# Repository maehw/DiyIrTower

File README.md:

# README

Can be used as a replacement of the original LEGO IR serial tower with programs and platforms such as

* [WebPBrick](https://www.webpbrick.com): web-based NQC IDE (see also: [github.com/maehw/WebPBrick/](https://github.com/maehw/WebPBrick/))
* [Bricx Command Center (BricxCC)](https://bricxcc.sourceforge.net/): 32-bit Windows IDE
* `firmdl3` command line download tool
* probably other software

to **load user programs and firmware** on the yellow LEGO Mindstorms RCX programmable brick.

## Hardware

> ⚠️ **Warning**: Exposure to infrared light can cause harm to humans. Prolonged or intense exposure may lead to damage to the eyes or skin. Always use proper safety equipment when working with infrared light sources. Make sure to limit the current through the infrared TX LED!

### Pin Assignment

At the heart of the DIY solution, there's an 8-pin ATtiny13A microcontroller.

Pin Assignment Table for the ATtiny13A:

| IC Pin | Pin    | Purpose              | Direction | Side of IC | ISP Usage |
|--------|--------|----------------------|-----------|------------|-----------|
| 1      | PB5    | Reset                | Unused    | Left       | Reset     |
| 2      | PB3    | IR_LED_TX_PIN        | Output    | Left       |           |
| 3      | PB4    | PHOTO_RX_PIN         | Input     | Left       |           |
| 4      | GND    | Ground               | -         | Left       | GND       |
| 5      | PB0    | UART_RX_PIN          | Output    | Right      | MOSI      |
| 6      | PB1    | UART_TX_PIN          | Input     | Right      | MISO      |
| 7      | PB2    | IR_ACTIVITY_LED_PIN  | Output    | Right      | SCK       |
| 8      | VCC    | Supply Voltage (VCC) | -         | Right      | VCC       |

The column "ISP Usage" shows what pins need to be connected for programming ("flashing") by a 6-pin AVR _In-System Programmer_ (ISP).

### Hardware Parts

- ATtiny13A microcontroller as the "brain" (calibrated internal 9.6 MHz oscillator as clock source; other uCs such as the ATtiny85 _may_ work as they have more SRAM and more flash memory, but timing values will need to be adjusted)
- Vishay Semiconductors TSOP4338 or TSOP4838 38 kHz infrared receiver (others 38 kHz infrared receivers _may_ work)
- Vishay Semiconductors TSAL6200 940 nm infrared TX LED (others 940 nm infrared TX LEDs _may_ work)

If you've built a working DiyIrTower yourself with these or different parts, please let me know! The first design has used the TSOP4338. As it's not available everywhere, it has also been tested to work with the TSOP4838.

In my case, the circuitry is powered by a USB/serial converter cable which is also used to transfer the data over a virtual COM port (USB CDC interface). Please note that the converter cable of choice uses TTL voltage levels and not RS-232!

### Classic Breadboard

For the breadboard version see the image at the top. The Fritzing breadboard diagram looks as follows (please also pay attention to the hints inside the image):

### Solder Breadboard

An alternative would be a solder breadboard to make something semi-permanent (the green activity LED is hidden in the next photo between the jumper wires of the USB/serial converter cable):

### CAD PCB with KiCAD

Since January 2026, there's a KiCAD project with all necessary files (i.e. schematic, PCB layout, pre-generated Gerber files). So instead of putting the components together on a breadboard, a PCB can be ordered. At the time of writing, some prototype PCBs (Rev. 1.0) have been ordered. But I cannot guarantee, that the design is free of bugs.

I've decided to keep through-hole components, as they are easier to solder for beginners. It may make sense to add a DIP8 IC socket for the uC. The power and activity LEDs (and their resistors) are optional, as is the ISP header for initially flashing the IC. So a setup with the minimum of components would look like this:

By the way, I'd choose a rectangular connector for J1. Also, you'll have to bend the TX photo diode D2 sideways, so that it points to the same side as the IR receiver IC.

## Firmware

Find the productive firmware in folder `./firmware`.

### Prerequisites

- GNU C cross-compiler for AVR 8-bit `gcc-avr` (other build toolchains *may* work as well)
- `avrdude`: program for downloading and uploading the on-chip memories of AVR microcontrollers (or another similar tool)

### Build

To build, run:

```shell
avr-gcc -g -Wall -Os -mmcu=attiny13a -o main.elf main.c
```

_(Append the verbosity flag `-v` to see what's going on behind the scenes.)_

Want to check if it will it fit into the internal flash?

```shell
avr-size main.elf
   text	   data	    bss	    dec	    hex	filename
    776	      0	      7	    783	    30f	main.elf
```

Make sure to burn the microcontrollers fuses so that

- the calibrated internal 9.6 MHz oscillator is selected
- clock pre-scaler set to 1 (device is shipped with CKDIV8 programmed).

Reading fuses with avrdude (and in this case an `ehajo-isp` in-system programmer):

```shell
avrdude -c ehajo-isp -p t13a -U hfuse:r:-:h -U lfuse:r:-:h
```

The default values for the two fuse bytes of the ATtiny13A are `0xff` (high), `0x6a` (low).  The required settings however are: `0xff` (high), `0x7a` (low). Writing fuses with avrdude:

```shell
avrdude -c ehajo-isp -p t13a -U hfuse:w:0xff:m -U lfuse:w:0x7a:m
```

_(Hint: If the `avrdude` version being used gives *"avrdude: AVR Part "t13a" not found."*, try using `t13` instead of `t13a`.)_

Finally, flash the firmware:

```shell
avrdude -c ehajo-isp -p t13a -U flash:w:main.elf:e
```

### Test firmware

Please note that under `./test/firmware`, there are some more code files to test the assembled hardware. The commands from above can be reused, only the filename needs to be changed.

`blink.c` will blink the activity indication LED and hence allow to check if the LED is working and the compilation and flashing mechanisms also work.

`pulsed_ir_tx.c` will blink the activity indication LED and also transmit modulated infrared light at 38 kHz for 0.5 seconds and then switch the transmitter off for another 0.5 seconds. This allows to check if the fuse bytes have been set correctly or the blinking is way slower and the default `CKDIV8` may not have been overwritten.

`serial_echo.c` will _echo_ the serially received UART characters. Please note that this example does not make use of any uC UART peripheral but only relies upon GPIO pin edge detection on the "UART" receive pin. This can be used with any terminal emulator that works with serial devices or with the Python script `/test/scripts/serial_coms.py` to send and receive binary data:

```shell
$ python serial_coms.py -h
usage: serial_coms.py [-h] serial_device data_to_send

Send binary data over serial and receive response.

positional arguments:
  serial_device  Name of the serial device (e.g., '/dev/ttyUSB0')
  data_to_send   Binary data to send in HEX format (e.g., '55FF00609F609F')

options:
  -h, --help     show this help message and exit
```

Example:

```shell
$ python serial_coms.py /dev/ttyUSB0 11223344
[TX] 11 22 33 44 
[RX] 11 22 33 44
```

The same four bytes should be received that also have been transmitted before - just as you'd expect from an echo application! Check the command line output!

## Design details

The following timing diagram shows four signals from top to bottom:

* `UART_TX_PIN`: the UART transmit (=TX) signal - as sent by the PC, coming from the attached USB/serial converter
* `IR_LED_TX_PIN`: the modulated infrared transmit signal on the IR TX LED, on–off keying (OOK) modulated at 38 kHz, 38 kHz carrier is _active_ during _low_ periods of `UART_TX_PIN`
* `PHOTO_RX_PIN`: the signal on the (already demodulated) infrared receiver
* `UART_RX_PIN`: the UART receive (=RX) signal - as sent by the DIY IR tower to the USB/serial converter

The diagram shows the message `0x55 0xFF 0x00 0x10 0xEF 0x10 0xEF` being sent from the PC to the RCX (left half). It also shows the response from the RCX to the PC: `0x55 0xFF 0x00 0xEF 0x10 0xEF 0x10` (right half).

In the left half one can also see that the signal transmitted by the DIY IR tower is reflected and directly received by itself. This is due to the arrangement of IR TX LED and IR receiver - and afair can also be seen with the original IR towers. This "echo effect" must/can be handled in software!

Zooming in (less time for the same screen width) reveals the delays between the signals:

## Disclaimer

LEGO® is a trademark of the LEGO Group of companies which does not sponsor, authorize or endorse this project.

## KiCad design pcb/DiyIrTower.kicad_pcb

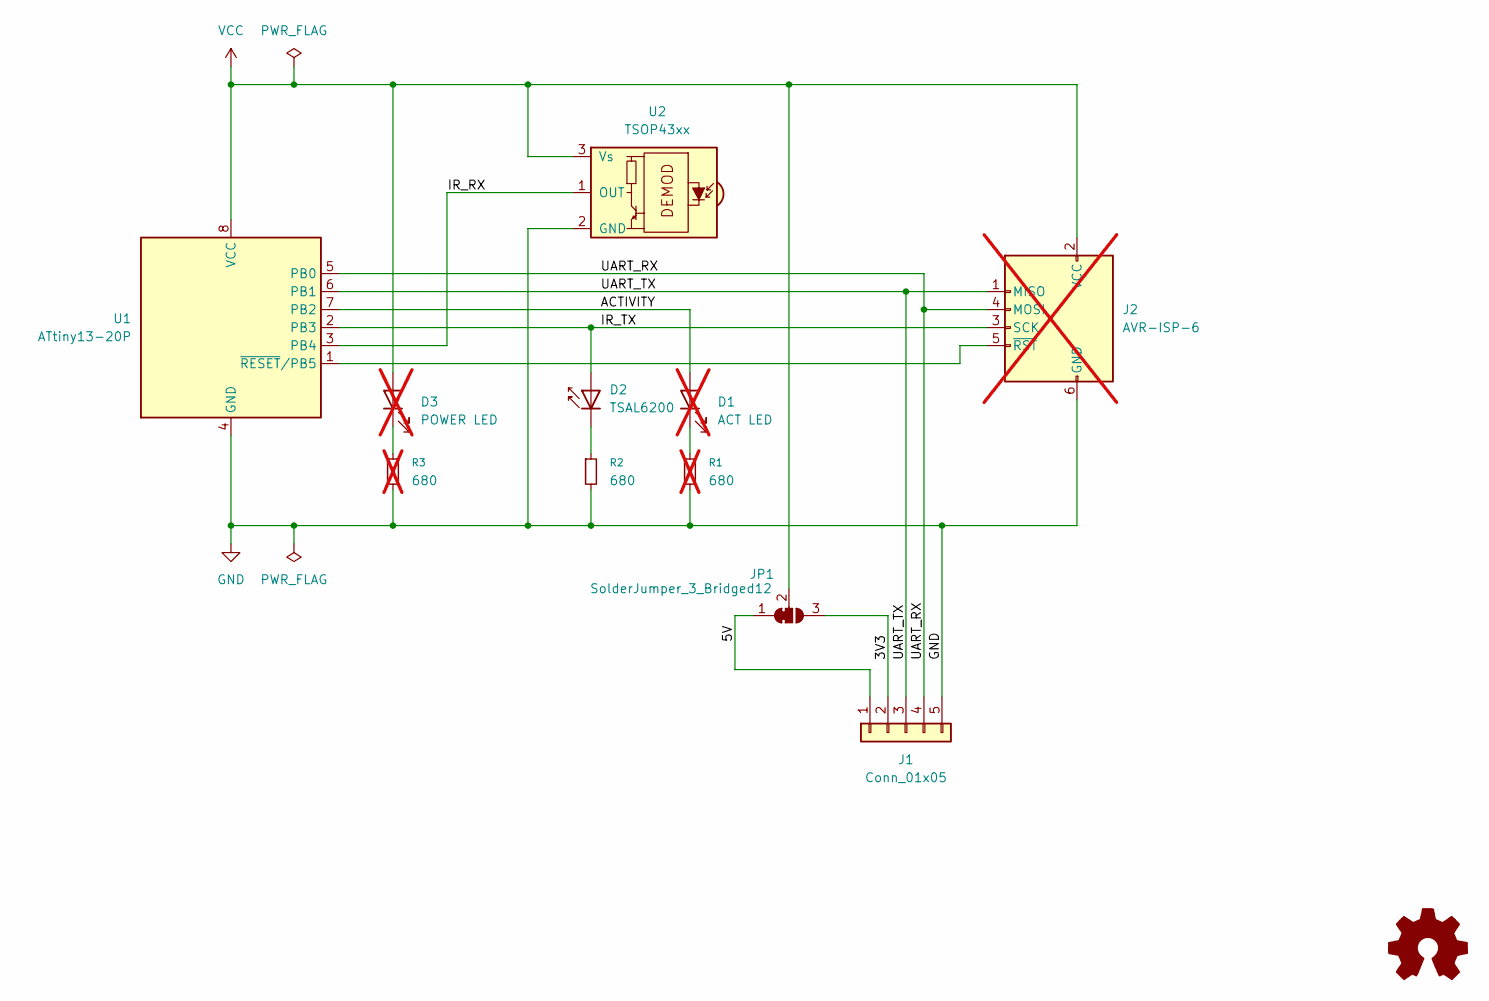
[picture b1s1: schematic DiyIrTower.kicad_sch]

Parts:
D1: ACT LED; LED_D3.0mm; not fitted
D2: TSAL6200; LED_D5.0mm_IRBlue
D3: POWER LED; LED_D3.0mm; not fitted
J1: Conn_01x05; PinSocket_1x05_P2.54mm_Vertical
J2: AVR-ISP-6; IDC-Header_2x03_P2.54mm_Vertical; not fitted
JP1: SolderJumper_3_Bridged12; SolderJumper-3_P1.3mm_Bridged2Bar12_RoundedPad1.0x1.5mm
R1, R3: 680; R_Axial_DIN0207_L6.3mm_D2.5mm_P10.16mm_Horizontal; not fitted
R2: 680; R_Axial_DIN0207_L6.3mm_D2.5mm_P10.16mm_Horizontal
U1: ATtiny13-20P; DIP-8_W7.62mm
U2: TSOP43xx; Vishay_MOLD-3Pin

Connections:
/3V3: J1.2, JP1.3 (B)
/5V: J1.1, JP1.1 (A)
/ACTIVITY: D1.2 (A), U1.7 (PB2)
/IR_RX: U1.3 (PB4), U2.1 (OUT)
/IR_TX: D2.2 (A), J2.3 (SCK), U1.2 (PB3)
/UART_RX: J1.4, J2.4 (MOSI), U1.5 (PB0)
/UART_TX: J1.3, J2.1 (MISO), U1.6 (PB1)
GND: J1.5, J2.6 (GND), R1.2, R2.2, R3.2, U1.4 (GND), U2.2 (GND)
unnamed: D1.1 (K), R1.1
unnamed: D2.1 (K), R2.1
unnamed: D3.1 (K), R3.1
unnamed: J2.5 (~RST), U1.1 (~RESET/PB5)
VCC: D3.2 (A), J2.2 (VCC), JP1.2 (C), U1.8 (VCC), U2.3 (Vs)

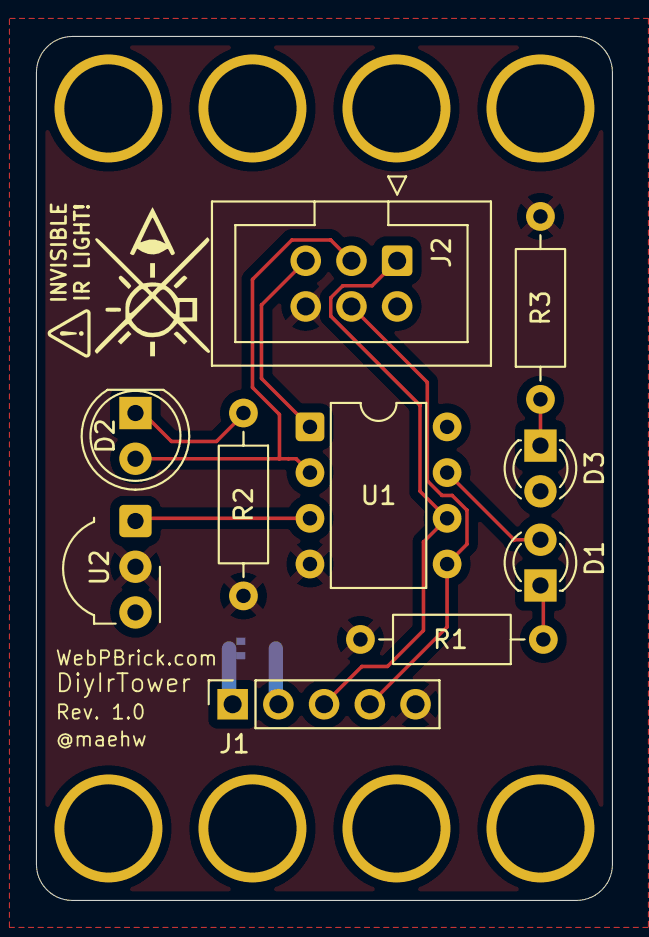
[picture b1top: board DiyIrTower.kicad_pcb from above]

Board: 2 copper layers, 32.0 x 48.0 mm, 13 parts (1 on the bottom side), 13 nets.

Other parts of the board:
MH: brick-1x4
MH#2: brick-1x4

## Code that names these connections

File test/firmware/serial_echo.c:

/*
 * DiyIrTower
 * Copyright (C) 2024 maehw
 *
 * This program is free software: you can redistribute it and/or modify
 * it under the terms of the GNU General Public License as published by
 * the Free Software Foundation, either version 3 of the License, or
 * (at your option) any later version.
 *
 * This program is distributed in the hope that it will be useful,
 * but WITHOUT ANY WARRANTY; without even the implied warranty of
 * MERCHANTABILITY or FITNESS FOR A PARTICULAR PURPOSE.  See the
 * GNU General Public License for more details.
 *
 * You should have received a copy of the GNU General Public License
 * along with this program.  If not, see <http://www.gnu.org/licenses/>.
 */

// This is just a classic "serial echo" example that should echo the received serial bytes back.
// Please note: no serial peripheral is involved, this is purely based on edge-detection.

#ifndef F_CPU
    #define F_CPU 9600000UL
#elif F_CPU != 9600000UL
    #error "F_CPU must be set to 9.6 MHz"
#endif

#include <avr/io.h>
#include <avr/interrupt.h>
#include <stdbool.h>

/*
 * Pin Assignment Table for the ATtiny13A:
 *
 * IC Pin | Pin  | Purpose               | Direction | Side of IC
 * --------------------------------------------------------------
 * 1      | PB5  | Reset                 | Unused    | Left
 * 2      | PB3  | Unused                | Unused    | Left
 * 3      | PB4  | Unused                | Unused    | Left
 * 4      | GND  | Ground                | -         | Left
 * 5      | PB0  | UART_RX_PIN           | Output    | Right
 * 6      | PB1  | UART_TX_PIN           | Input     | Right
 * 7      | PB2  | IR_ACTIVITY_LED_PIN   | Output    | Right
 * 8      | VCC  | Supply Voltage (VCC)  | -         | Right
 */

/*
 * Make sure to burn the fuses so that
 * - the calibrated internal 9.6 MHz oscillator is selected
 * - clock pre-scaler set to 1 (device is shipped with CKDIV8 programmed; which is not what we want).
 *
 * Reading fuses with avrdude (and in this case an ehajo-isp):
 *   avrdude -c ehajo-isp -p t13a -U hfuse:r:-:h -U lfuse:r:-:h
 * The default is: 0xff (high), 0x6a (low)
 *
 * The required setting is: 0xff (high), 0x7a (low)
 * Writing fuses with avrdude:
 *   avrdude -c ehajo-isp -p t13a -U hfuse:w:0xff:m -U lfuse:w:0x7a:m
 * Note: The setting is not really relevant for this example because even CKDIV8 should be fast enough.
 *
 * Compile and link it like this:
 *   avr-gcc -g -Wall -Os -mmcu=attiny13a -o serial_echo.elf serial_echo.c
 * Flash it:
 *   avrdude -c ehajo-isp -p t13a -U flash:w:serial_echo.elf:e
 */

#define UART_TX_PIN          PB1 // GPIO input pin for enabling modulation
#define UART_RX_PIN          PB0 // GPIO output pin that mirrors the input from the photo-transistor
#define ACTIVITY_LED_PIN     PB2 // GPIO output pin for indicating activity on the serial line(s)

#define MODULATION_FREQ                 38000 // 38 kHz
#define MODULATION_HALF_PERIOD          (F_CPU / (2 * MODULATION_FREQ)) // Calculate the half period in clock cycles; make sure that we really get this to ~2*38 kHz here
#define LED_UPDATE_FREQ                 1000 // 1 kHz
#define ACTIVITY_LED_ON_DURATION        160 // Duration in milliseconds for activity status LED to be ON for RX/TX

volatile uint8_t activity_led_counter = 0;
volatile uint8_t prev_uart_tx_state = 0;

void pin_change(bool on_init);

void setup() {
    // Set activity status LED pin and UART RX pin as outputs
    DDRB |= (1 << ACTIVITY_LED_PIN) | (1 << UART_RX_PIN);

    // Set enable pin as input
    DDRB &= ~(1 << UART_TX_PIN);

    // Enable internal pull-up resistor for enable pin and photo-transistor input pin
    PORTB |= (1 << UART_TX_PIN);

    // Enable Pin Change Interrupt for PHOTO_RX_PIN (PB4) and UART_TX_PIN (PB1)
    GIMSK |= (1 << PCIE); // Enable Pin Change Interrupt
    PCMSK |= (1 << PCINT1); // Enable Pin Change Interrupt on UART_TX_PIN (PB1)

    // Configure Timer0 for 38 kHz modulation frequency
    TCCR0A |= (1 << WGM01); // CTC mode
    OCR0A = MODULATION_HALF_PERIOD - 1; // Set the compare value for the desired modulation frequency
    TIMSK0 |= (1 << OCIE0A); // Enable Timer0 compare match A interrupt

    // Initialize to correct state
    pin_change(true);

    TCCR0B |= (1 << CS00); // Start Timer0 without pre-scaler (i.e. runs with F_CPU)
}

void pin_change(bool on_init) {
    // Get current state of pin UART_TX_PIN for proper edge detection
    uint8_t current_uart_tx_state = PINB & (1 << UART_TX_PIN);

    if ((current_uart_tx_state != prev_uart_tx_state) || on_init) {
        // UART_TX_PIN state has changed
        if (current_uart_tx_state) {
            // Rising edge detected on UART_TX_PIN

            // Also set UART_RX_PIN high
            PORTB |= (1 << UART_RX_PIN);
        } else {
            // Falling edge detected on UART_TX_PIN

            // Also set UART_RX_PIN low
            PORTB &= ~(1 << UART_RX_PIN);

            // Re-set duration for activity status LED to be on
            activity_led_counter = (ACTIVITY_LED_ON_DURATION > activity_led_counter) ? ACTIVITY_LED_ON_DURATION : activity_led_counter;

            // Turn on activity status LED
            PORTB |= (1 << ACTIVITY_LED_PIN);
        }
    }

    // Update previous state variables
    prev_uart_tx_state = current_uart_tx_state;
}

ISR(PCINT0_vect) {
    pin_change(false);
}

ISR(TIM0_COMPA_vect) {
    // Check if it's time to update LED counters
    static uint8_t led_counter = 0;
    led_counter++;
    if (led_counter >= ((2 * MODULATION_FREQ)/LED_UPDATE_FREQ)) {
        // Reset the counter
        led_counter = 0;

        // Update LED counters: check if activity status LED needs to be switched off again (should be on right now)
        if (activity_led_counter > 0) {
            activity_led_counter--;
            if (activity_led_counter == 0) {
                PORTB &= ~(1 << ACTIVITY_LED_PIN);
            }
        }
    }
}

int main() {
    setup();
    sei(); // Enable global interrupts

    while (1) {
        // Main loop remains idle
    }

    return 0;
}

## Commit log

2024-04-19 Add firmware and more details in README.md
2024-10-22 Update README.md: update parts list (uC + infrared)
2024-10-22 Add Fritzing breadboard diagram
2024-10-22 Update README.md: add Fritzing breadboard image
2024-10-22 Rename solder-breadboard_bottom-small.jpg to solder-breadboard_top.jpg
2024-10-22 Rename solder-breadboard_top-small.jpg to solder-breadboard_bottom.jpg
2024-10-22 Update README.md: add solder breadboard images
2024-10-22 Update README.md: add ISP info to pin assignment
2024-10-22 Update README.md: elaborate on fuse bytes and available test code
2024-10-23 Update documentation and blinky example
2024-10-23 Clean-up UART echo test firmware and documentation
2024-10-25 Add warning about infrared light
2024-10-28 Improve documentation: add details about signals
2024-10-29 Fix documentation about fuse bytes; add another example
2026-01-06 Slightly improve wording
2026-01-26 Add KiCAD 9.0 PCB design and update README.md for it
2026-01-31 Add license (CERN Open Hardware Licence Version 2 - Weakly Reciprocal) to PCB
2026-02-08 TSOP4838 IR receivers works too
2026-02-08 Add note about TTL and RS-232
